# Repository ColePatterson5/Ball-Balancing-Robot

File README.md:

# Ball-Balancing-Robot
Ball balancing robot made for ME556: Mechatronics. Somewhat works. Code and some Kicad files for custom PCB. Not sure where the schematic and pcb files have gone.

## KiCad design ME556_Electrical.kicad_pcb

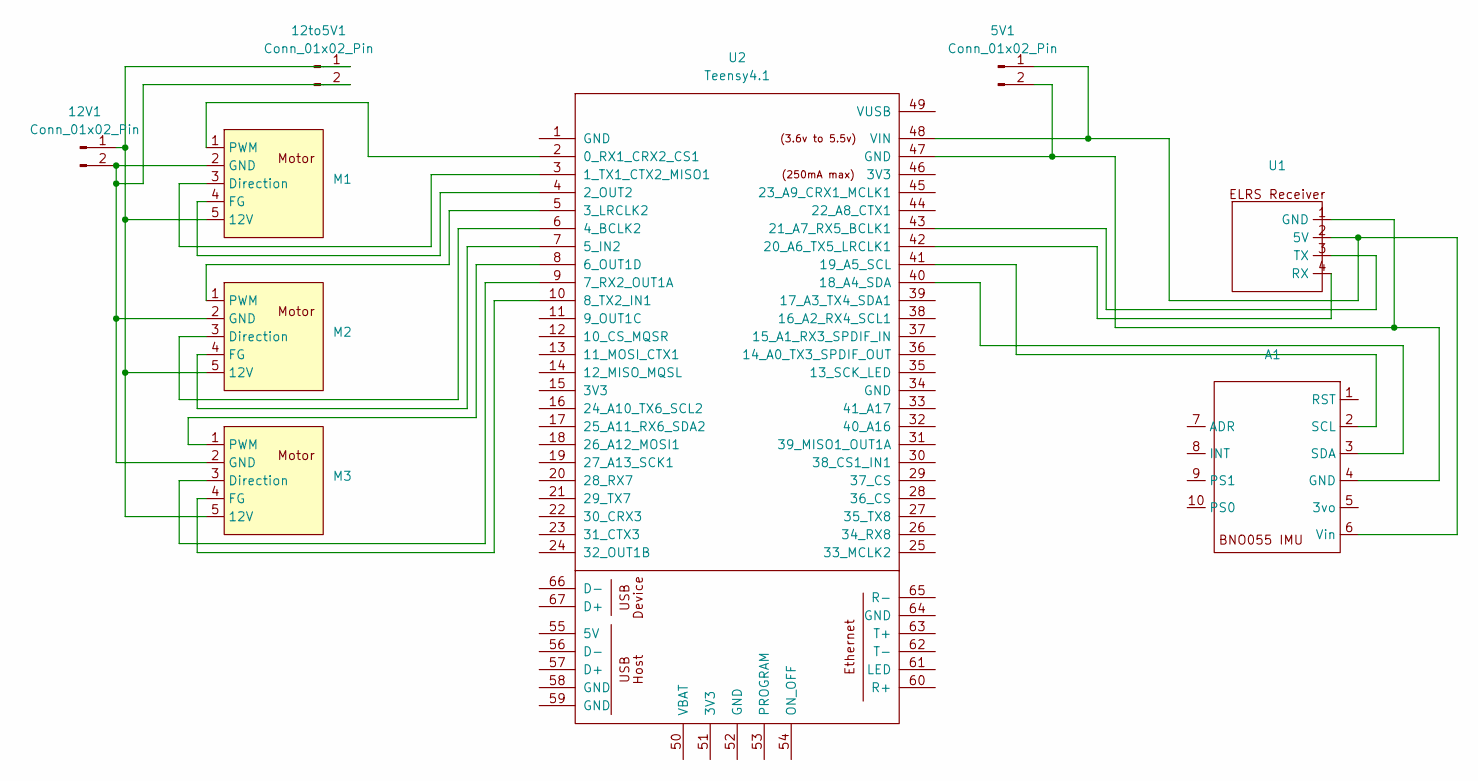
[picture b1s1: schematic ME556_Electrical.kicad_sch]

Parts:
5V1, 12to5V1: Conn_01x02_Pin; PinHeader_1x02_P2.54mm_Vertical
12V1: Conn_01x02_Pin; Power_Pads
A1: BNO055
M1, M2, M3: FIT0441_Motor_Pads
U1: ELRS_Receiver
U2: Teensy4.1; Teensy41

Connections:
unnamed: 5V1.1, A1.6 (Vin), U1.2 (5V), U2.48 (VIN)
unnamed: 5V1.2, A1.4 (GND), U1.1 (GND), U2.47 (GND)
unnamed: 12V1.1, 12to5V1.1, M1.5 (12V), M2.5 (12V), M3.5 (12V)
unnamed: 12V1.2, 12to5V1.2, M1.2 (GND), M2.2 (GND), M3.2 (GND)
unnamed: A1.2 (SCL), U2.41 (19_A5_SCL)
unnamed: A1.3 (SDA), U2.40 (18_A4_SDA)
unnamed: M1.3 (Direction), U2.3 (1_TX1_CTX2_MISO1)
unnamed: M1.4 (FG), U2.4 (2_OUT2)
unnamed: M1.1 (PWM), U2.2 (0_RX1_CRX2_CS1)
unnamed: M2.3 (Direction), U2.6 (4_BCLK2)
unnamed: M2.4 (FG), U2.7 (5_IN2)
unnamed: M2.1 (PWM), U2.5 (3_LRCLK2)
unnamed: M3.3 (Direction), U2.9 (7_RX2_OUT1A)
unnamed: M3.4 (FG), U2.10 (8_TX2_IN1)
unnamed: M3.1 (PWM), U2.8 (6_OUT1D)
unnamed: U1.4 (RX), U2.42 (20_A6_TX5_LRCLK1)
unnamed: U1.3 (TX), U2.43 (21_A7_RX5_BCLK1)

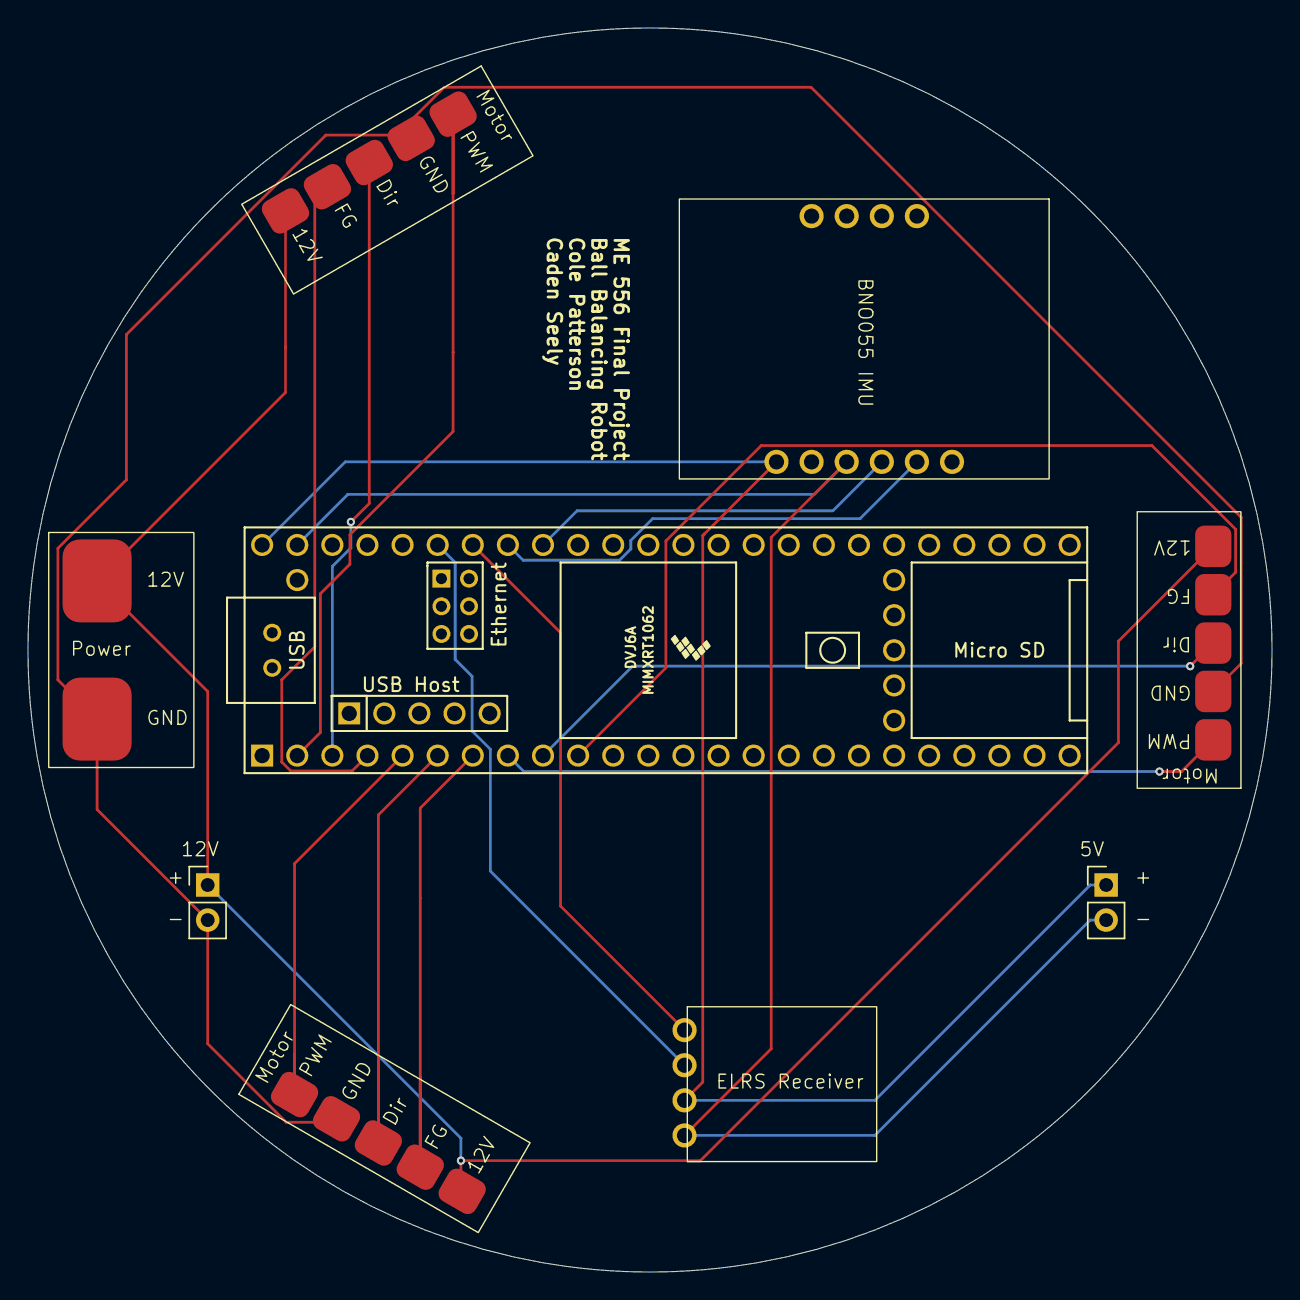
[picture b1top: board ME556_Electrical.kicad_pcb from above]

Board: 2 copper layers, 90.0 x 90.0 mm, 9 parts (0 on the bottom side), 17 nets.
